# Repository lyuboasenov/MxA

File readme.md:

# MxA

MxA is a portable BLE-enabled strain gauge that can be used for weight-free training as well as testing/assessment.

## Hardware technical specification

The hardware is based on ESP32-WROOM module, HX711 amplifier and S-type strain gauge.

[Read more...](docs/hardware.md)

**DIY** You can assemble the device from pre-built modules
[DIY](docs/diy.md)

## Firmware

[Read more...](docs/firmware.md)

## Mobile application

*TBA*

[Read more...](docs/mobile-app.md)

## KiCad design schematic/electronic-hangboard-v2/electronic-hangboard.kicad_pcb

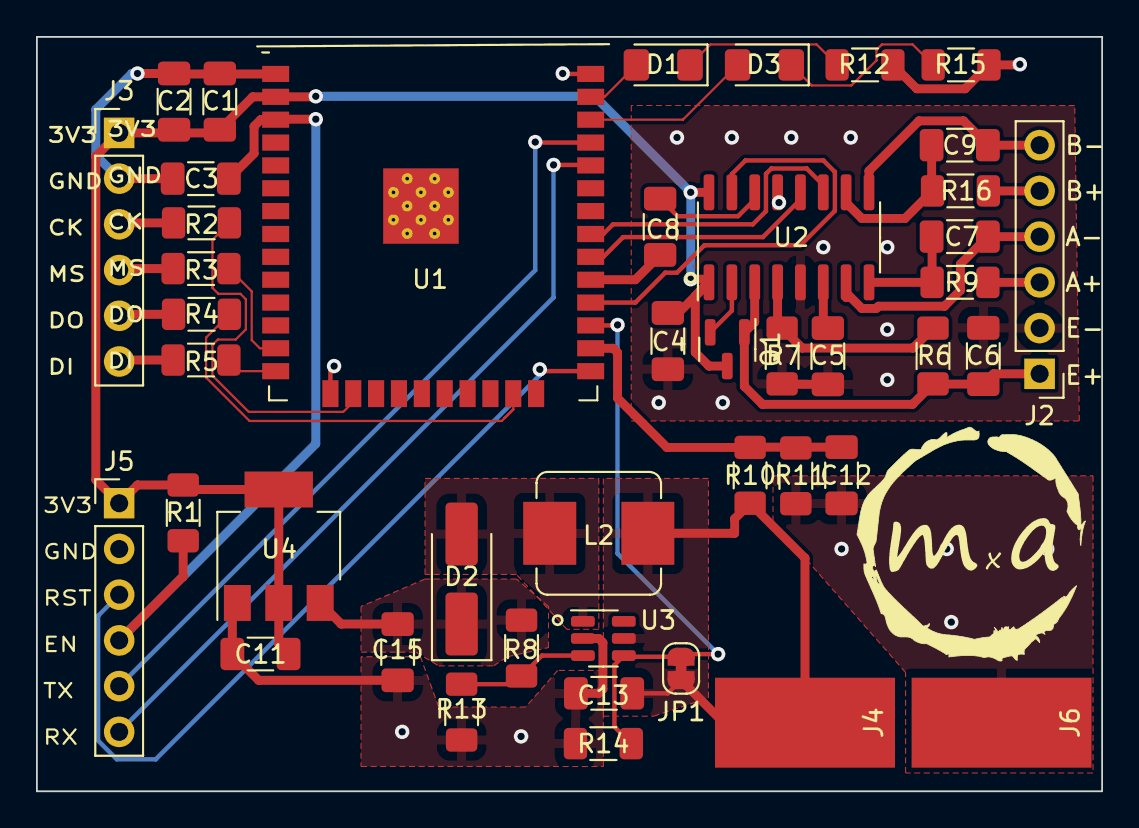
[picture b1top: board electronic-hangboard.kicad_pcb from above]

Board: 2 copper layers, 59.2 x 41.9 mm, 44 parts (0 on the bottom side), 39 nets.

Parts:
C1, C3, C5, C7, C9: 0.1uF; C_1206_3216Metric_Pad1.33x1.80mm_HandSolder
C2, C4, C6: 10uF; C_1206_3216Metric_Pad1.33x1.80mm_HandSolder
C8: 22pF; C_1206_3216Metric_Pad1.33x1.80mm_HandSolder
C11, C13, C15: 22uF; C_1206_3216Metric_Pad1.33x1.80mm_HandSolder
C12: 100nF; C_1206_3216Metric_Pad1.33x1.80mm_HandSolder
D1, D3: LED; D_1206_3216Metric_Pad1.42x1.75mm_HandSolder
D2: SS34; D_SMA_Handsoldering
J2: Conn_01x04_Pin; PinHeader_1x06_P2.54mm_Vertical
J3: JTAG; PinHeader_1x06_P2.54mm_Vertical
J4, J6: Conn_01x01_Pin; SolderWirePad_1x01_SMD_5x10mm
J5: UART; PinHeader_1x06_P2.54mm_Vertical
JP1: Jumper_2_Bridged; SolderJumper-2_P1.3mm_Bridged_RoundedPad1.0x1.5mm
L2: 22uH; L_Bourns_SRP7028A_7.3x6.6mm
Q1: S9015; SOT-23
R1, R6, R14: 10K; R_1206_3216Metric_Pad1.30x1.75mm_HandSolder
R2, R3, R4, R5: 100R; R_1206_3216Metric_Pad1.30x1.75mm_HandSolder
R7: 8K2; R_1206_3216Metric_Pad1.30x1.75mm_HandSolder
R8: 110K; R_1206_3216Metric_Pad1.30x1.75mm_HandSolder
R9, R16: 1K2; R_1206_3216Metric_Pad1.30x1.75mm_HandSolder
R10: 1M; R_1206_3216Metric_Pad1.30x1.75mm_HandSolder
R11: 330K; R_1206_3216Metric_Pad1.30x1.75mm_HandSolder
R12, R15: 330R; R_1206_3216Metric_Pad1.30x1.75mm_HandSolder
R13: 15K; R_1206_3216Metric_Pad1.30x1.75mm_HandSolder
U1: ESP32-WROOM-32
U2: HX711; SOP-16_3.9x9.9mm_P1.27mm
U3: MT3608; SOT-23-6
U4: AMS1117-3.3; SOT-223-3_TabPin2

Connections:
+3V3: C1.1, C2.1, C4.1, C11.2, J3.1, J5.1, Q1.3 (E), R1.1, U1.2 (VDD), U2.1 (VSUP), U2.16 (DVDD), U4.2 (VO)
+5V: C15.2, D2.1 (K), R8.1, U4.3 (VI)
+BATT: C13.2, J4.1, JP1.2 (B), L2.1, R10.1, U3.5 (IN)
A+: J2.3, R9.1
A-: C7.2, J2.4, U2.7 (INA-)
B+: J2.5, R16.1
B-: C9.2, J2.6, U2.9 (INB-)
BATT_REF: C12.1, R10.2, R11.1, U1.26 (IO4)
CONV_EN: JP1.1 (A), R14.1, U1.27 (IO16), U3.4 (EN)
DOUT: U1.30 (IO18), U2.12 (DOUT)
E+: C6.2, J2.1, Q1.1 (C), R6.1, U2.3 (AVDD)
E-: C1.2, C2.2, C3.1, C4.2, C5.1, C6.1, C11.1, C12.2, C13.1, C15.1, J2.2, J3.2, J5.2, J6.1, R7.2, R11.2, R12.1, R13.2, R14.2, R15.2, U1.1 (GND), U1.15 (GND), U1.38 (GND), U1.39 (GND), U2.5 (AGND), U2.13 (XO), U3.2 (GND), U4.1 (GND)
EN: C3.2, J5.4, R1.2, U1.3 (EN)
HX711_SCK: U1.31 (IO19), U2.11 (PD_SCK)
IO22: D3.2 (A), U1.36 (IO22)
IO23: D1.2 (A), U1.37 (IO23)
MTCK: R2.2, U1.16 (IO13)
MTDI: R5.2, U1.14 (IO12)
MTDO: R4.2, U1.23 (IO15)
MTMS: R3.2, U1.13 (IO14)
unnamed: D1.1 (K), R12.2
unnamed: D2.2 (A), L2.2, U3.1 (SW)
unnamed: D3.1 (K), R15.1
unnamed: J3.3, R2.1
unnamed: J3.4, R3.1
unnamed: J3.5, R4.1
unnamed: J3.6, R5.1
unnamed: Q1.2 (B), U2.2 (BASE)
unnamed: C7.1, R9.2, U2.8 (INA+)
unnamed: C9.1, R16.2, U2.10 (INB+)
unnamed: C5.2, U2.6 (VBG)
unnamed: R6.2, R7.1, U2.4 (VFB)
unnamed: C8.1, U2.14 (XI)
unnamed: R8.2, R13.1, U3.3 (FB)
RST: J5.3, U1.25 (IO0)
RX: J5.6, U1.34 (RXD0/IO3)
TX: J5.5, U1.35 (TXD0/IO1)
XTAL: C8.2, U1.29 (IO5)
XTAL_EN: U1.28 (IO17), U2.15 (RATE)

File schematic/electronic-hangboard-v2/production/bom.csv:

Designator,Footprint,Quantity,Value,LCSC Part #
"C1, C3, C5, C7, C9",1206,5,0.1uF,
"C11, C13, C15",1206,3,22uF,
C12,1206,1,100nF,
"C2, C4, C6",1206,3,10uF,
C8,1206,1,22pF,
"D1, D3",1206,2,LED,
D2,D_SMA_Handsoldering,1,SS34,
J2,PinHeader_1x06_P2.54mm_Vertical,1,Conn_01x04_Pin,
J3,PinHeader_1x06_P2.54mm_Vertical,1,JTAG,
"J4, J6",SolderWirePad_1x01_SMD_5x10mm,2,Conn_01x01_Pin,
J5,PinHeader_1x06_P2.54mm_Vertical,1,UART,
JP1,SolderJumper-2_P1.3mm_Bridged_RoundedPad1.0x1.5mm,1,Jumper_2_Bridged,
L2,L_Bourns_SRP7028A_7.3x6.6mm,1,22uH,
Q1,SOT-23,1,S9015,
"R1, R14, R6",1206,3,10K,
R10,1206,1,1M,
R11,1206,1,330K,
"R12, R15",1206,2,330R,
R13,1206,1,15K,
"R16, R9",1206,2,1K2,
"R2, R3, R4, R5",1206,4,100R,
R7,1206,1,8K2,
R8,1206,1,110K,
U1,ESP32-WROOM-32,1,ESP32-WROOM-32,
U2,SOP-16_3.9x9.9mm_P1.27mm,1,HX711,
U3,SOT-23-6,1,MT3608,
U4,SOT-223-3_TabPin2,1,AMS1117-3.3,

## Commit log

2023-05-19 migrate to esp32
2023-05-19 add ble
2023-05-20 refactor ble
2023-05-20 refactor load cell
2023-05-21 add mobile app initial
2023-05-22 timer work
2023-05-22 connect hangboard initial
2023-05-23 poc is finito
2023-06-08 logo
2023-06-08 change logo
2023-06-08 update deps & install material design
2023-06-09 small refactoring
2023-06-09 disable buttons when not active
2023-06-09 refactor timer
2023-06-09 rename browse to trainings
2023-06-09 fix sets progress
2023-06-09 visual
2023-06-09 adding new training
2023-06-15 Update pcb
2023-06-15 add battery level ble service
2023-06-15 update schematic fix voltage divider not connected
2023-06-15 asdf
2023-06-15 report battery level
2023-06-15 read battery level in the app
2023-06-15 add enclosure
2023-06-15 Enable settings of weight
2023-06-18 rename change icons add themes
2023-06-18 add flyout icons
2023-06-18 this and that
2023-06-19 improve themes
2023-06-19 handle orientation
2023-06-26 somewhat working
2023-06-26 get workouts working
2023-06-26 асдф
2023-06-27 almost getting the timer working again
2023-07-01 add timer state machine
2023-07-01 timer refactor
2023-07-02 enabe next/prev
2023-07-05 View exercises
2023-07-05 skip zero periods
2023-07-06 save activity log
2023-07-06 add activity log report
2023-07-06 record some of the rest as well
2023-07-06 Report improvements
2023-07-06 cleanup
2023-07-06 search somewhat works
2023-07-06 fix search box
2023-07-07 edit workout activities
2023-07-07 fix search
2023-07-11 Skip last rep rest if set rest is gt 0
2023-07-11 Details expanded by default
2023-07-11 order events by sets then by reps
2023-07-12 complete and cancel timer
2023-07-12 add additional details
2023-07-12 export logbook
2023-07-12 export logs and display where have been saved
2023-07-12 fix toolbar icons
2023-07-12 Remove timer back button
2023-07-12 add timestamp to exported file
2023-07-13 fix timer navigation
2023-07-13 bump package referenes
2023-07-13 change target framework
2023-07-13 move previous period rest
2023-07-13 navigation fixes
2023-07-13 copy to clipboard
2023-07-13 Sound and color settings
2023-07-13 update about page
2023-07-15 fix timer complete
2023-07-15 expand log entry date to fit activities
2023-07-18 remove user file
2023-09-19 add readme
2023-09-19 add images
2023-09-24 rework the schematic using mt3608 dc-dc convert
2023-09-24 add led indicators
2023-09-24 move panelized board in folder
2023-09-25 update schematic
2023-09-25 docs update
2023-09-25 image size
2023-09-25 add firmware and some hardware documentation
2023-09-25 fix links
2023-09-26 add diy modules
2023-09-26 diy images
2023-09-26 diy add battery monitor
2023-10-01 update docs
2023-10-01 update HX711 mod
2023-10-01 add hx711 reference
2024-02-04 live view
2024-02-04 Simplifying the workout model. Everything is broken.
2024-07-25 Add live view control
2024-07-30 OTA update
2024-08-15 small firm tweaks
2024-08-28 schematic autosave
2024-08-28 initial publish
2024-08-28 feature graphic
2024-08-28 schematic export
2024-08-28 require scan and connect bluetooth permissions
2024-09-14 schematic checkout
2024-09-14 App small fixes
2024-09-14 Return back location permissions
2024-09-15 Fix hangs
2024-09-15 Bump version
2024-10-06 Permission per android version
